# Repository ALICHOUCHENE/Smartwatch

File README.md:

<div align="center"><h1 style="font-family: courier;" align="center"></h1></div>

# Description
Smartwatch circuit for health and fitness
This robust fitness watch was designed for football players who leads an active lifestyle and values health and well-being. 
The watch creates for a personal training plan that adapts to some fitness needs. 
This smart-watch will provide a real-time guidance while exercising to help the player at the right intensity.
24/7 activity tracking with steps, calories and sleep, together with stress and recovery monitoring, provide a real time heart rate monitoring and help to maintain a healthy balance between activity and rest.

Here the features of the board:

- Xtensa dual-core 32-bit LX6 microprocessor(WROOM-32D) is the CPU of the board. operating at 240 MHz.
- Optical Sensor IC,BH1792GLC, a heart rate monitor module integrated with LED driver, green light, and IR detection photodiode.
- 1Cell / 3.7V 230mA Battery Management System / BMS Over Voltage, Over Current, Short Circuit Protection Module for Lithium ION Batterie.
- UART programming interface.
- I2C interface for OLED display.
- USB port for charging.

# PCB Layout : 

# Board 3D view : 

# Final Poduct : 

 # Manufacturing
 
After finishing the Routing and verify the pcb. We made the board at JLC PCB and we chose also the PCB Assembly service.
Here is the **[BOM](https://github.com/ALICHOUCHENE/Smartwatch-/blob/main/Assembly/BOM.csv)** needed for jlcpcb assembly service:

| Designator | Value           | Footprint                                                                        | LCSC Part |
|------------|-----------------|----------------------------------------------------------------------------------|-----------|
| U2         | TP4056          | Package_SO:SO-8_3.9x4.9mm_P1.27mm                                                | C16581    |
| R5         | 1.2K            | 402                                                                              |  C25862   |
| R7         | 1K              | 402                                                                              | C11702    |
| R8         | 1K              | 402                                                                              | C11702    |
| R4         | 1K              | 402                                                                              | C11702    |
| C2         | 0.1UF           | 402                                                                              |  C1525    |
| R6         | 100             | 402                                                                              |  C25076   |
| C3         | 0.1UF           | 402                                                                              |  C1525    |
| U1         | FS8205A         | Package_SO:TSSOP-8_4.4x3mm_P0.65mm                                               | C16052    |
| R2         | 3.3K            | 402                                                                              |  C25890   |
| R3         | 3.3K            | 402                                                                              |  C25890   |
| R1         | 3.3K            | 402                                                                              |  C25890   |
| C4         | 100nF           | 402                                                                              |  C1525    |
| R9         | 10K             | 402                                                                              |  C25744   |
| U4         | ESP32-WROOM-32D | RF_Module:ESP32-WROOM-32                                                         |           |
| U3         | DW01-P          | Package_TO_SOT_SMD:SOT-23-6                                                      | C181096   |
| C1         | 0.1UF           | 402                                                                              |  C1525    |
| J1         | USB_OTG         | Connector_USB:USB_Mini-B_Lumberg_2486_01_Horizontal                              | C136451   |
| BZ1        | Buzzer          | Buzzer_Beeper:Buzzer_Murata_PKMCS0909E4000-R1                                    | C255319   |
| R11        | 330             | 402                                                                              |  C25104   |
| R10        | 330             | 402                                                                              |  C25104   |
| SW1        | SW_DIP_x01      | Button_Switch_SMD:SW_DIP_SPSTx01_Slide_6.7x4.1mm_W6.73mm_P2.54mm_LowProfile_JPin | C54948    |
| D2         | LED             | 402                                                                              |           |
| D4         | LED             | 402                                                                              |           |
| D3         | LED             | 402                                                                              |           |
| Q2         | BC847           | Package_TO_SOT_SMD:SOT-23                                                        | C8664     |
| Q3         | BC847           | Package_TO_SOT_SMD:SOT-23                                                        | C8664     |
| U5         | AMS1117-3.3     | Package_TO_SOT_SMD:TSOT-23                                                       | C83932    |
| C5         | 0.1UF           | 402                                                                              |  C1525    |

# Downloads

* [Board schematics](https://github.com/ALICHOUCHENE/Smartwatch-/blob/main/Schematic.pdf)

* [PCB layout](https://github.com/ALICHOUCHENE/Smartwatch-/blob/main/Smartwatch.kicad_pcb)

* [BOM](https://github.com/ALICHOUCHENE/Smartwatch-/blob/main/Assembly/BOM.csv)

* [Position file](https://github.com/ALICHOUCHENE/Smartwatch-/blob/main/Assembly/Smartwatch-all-pos.csv)

* [Gerber File](https://github.com/ALICHOUCHENE/Smartwatch-/blob/main/Gerber/Gerber.rar)

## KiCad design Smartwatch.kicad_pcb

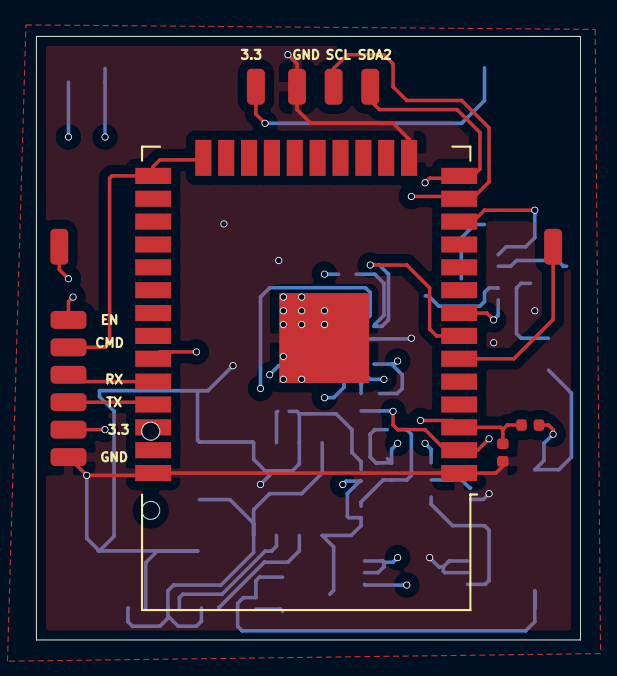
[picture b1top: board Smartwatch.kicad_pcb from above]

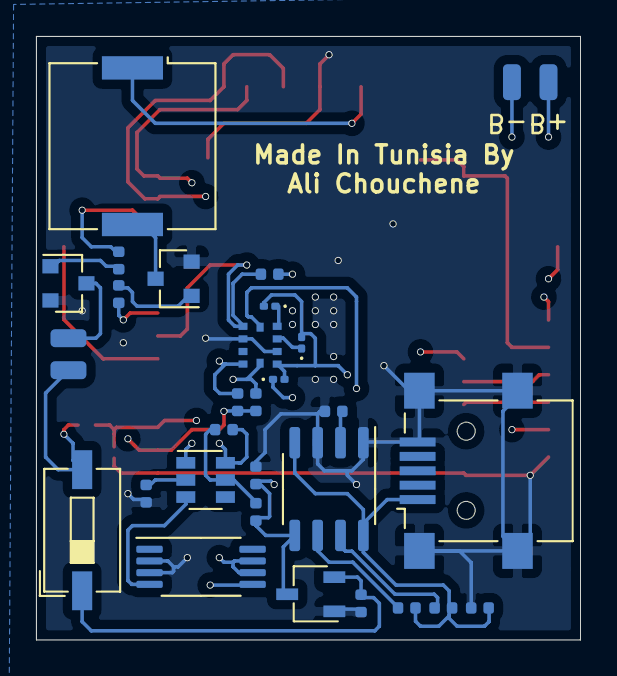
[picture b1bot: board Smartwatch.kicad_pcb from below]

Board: 4 copper layers, 30.2 x 33.5 mm, 46 parts (31 on the bottom side), 31 nets.

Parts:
BZ1: Buzzer; Buzzer_Murata_PKMCS0909E4000-R1
C1, C2, C3, C5: 0.1UF; C_0402_1005Metric
C4: 100nF; C_0402_1005Metric
D2, D3, D4: LED; LED_0201_0603Metric
IC1: BH1792GLC-E2; WLG
J1: USB_OTG; USB_Mini-B_Lumberg_2486_01_Horizontal
J2, J3, J4, J5, J6, J7, J8, J9, J10, J11, J12, J13, J14, J15, J16, J17: Conn_01x01_Female; SolderWirePad_1x01_SMD_1x2mm
Q2, Q3: BC847; SOT-23
R1, R2, R3: 3.3K; R_0402_1005Metric
R4, R7, R8: 1K; R_0402_1005Metric
R5: 1.2K; R_0402_1005Metric
R6: 100; R_0402_1005Metric
R9: 10K; R_0402_1005Metric
R10, R11: 330; R_0402_1005Metric
SW1: SW_DIP_x01; SW_DIP_SPSTx01_Slide_6.7x4.1mm_W6.73mm_P2.54mm_LowProfile_J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
U1: FS8205A; TSSOP-8_4.4x3mm_P0.65mm
U2: TP4056; SO-8_3.9x4.9mm_P1.27mm
U3: DW01-P; SOT-23-6
U4: ESP32-WROOM-32D; ESP32-WROOM-32
U5: AMS1117-3.3; TSOT-23

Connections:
+3V3: BZ1.1, D2.2, D3.2, D4.2, IC1.1, J4.1, J8.1, J16.1, R1.1, R2.1, R3.1, R9.1, SW1.2, U4.2
+5V: C1.1, J1.1, R7.1, R8.1, U2.4, U2.8
B1: J3.1, U4.6
B2: J2.1, U4.33
B+: C3.1, J14.1, R6.1, U2.5, U5.3
B-: C2.1, J13.1, U1.6, U1.7, U3.6
CMD: J11.1, U4.24, U4.25
EN: C4.1, J12.1, R9.2, U4.3
GND: C1.2, C3.2, C4.2, C5.2, IC1.2, IC1.7, J1.5, J1.6, J5.1, J15.1, Q2.2, Q3.2, R4.2, R5.1, U1.2, U1.3, U2.1, U2.3, U4.1, U4.15, U4.38, U4.39, U5.1
unnamed: BZ1.2, Q3.3
unnamed: C2.2, R6.2, U3.5
unnamed: C5.1, SW1.1, U5.2
unnamed: D2.1, IC1.3
unnamed: D3.1, IC1.4
unnamed: D4.1, IC1.5
unnamed: J17.1, Q2.3
unnamed: Q2.1, R10.1
unnamed: Q3.1, R11.1
unnamed: R4.1, U3.2
unnamed: R5.2, U2.2
unnamed: R7.2, U2.7
unnamed: R8.2, U2.6
OC: U1.4, U3.3
OD: U1.5, U3.1
RX: J10.1, U4.34
SC: IC1.6, R1.2, U4.7
SCL: IC1.10, J7.1, R3.2, U4.13
SDA2: IC1.9, J6.1, R2.2, U4.14
TX: J9.1, U4.35
bz: R11.2, U4.8
mt: R10.2, U4.12

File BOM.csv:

Designator,value,footprint,LCSC Part 
U2,TP4056,Package_SO:SO-8_3.9x4.9mm_P1.27mm,C16581
R5,1.2K,402, C25862
R7,1K,402,C11702
R8,1K,402,C11702
R4,1K,402,C11702
C2,0.1UF,402, C1525
R6,100,402, C25076
C3,0.1UF,402, C1525
U1,FS8205A,Package_SO:TSSOP-8_4.4x3mm_P0.65mm,C16052
R2,3.3K,402, C25890
R3,3.3K,402, C25890
R1,3.3K,402, C25890
C4,100nF,402, C1525
R9,10K,402, C25744
U4,ESP32-WROOM-32D,RF_Module:ESP32-WROOM-32,
U3,DW01-P,Package_TO_SOT_SMD:SOT-23-6,C181096
C1,0.1UF,402, C1525
J1,USB_OTG,Connector_USB:USB_Mini-B_Lumberg_2486_01_Horizontal,C136451
BZ1,Buzzer,Buzzer_Beeper:Buzzer_Murata_PKMCS0909E4000-R1,C255319
R11,330,402, C25104
R10,330,402, C25104
SW1,SW_DIP_x01,Button_Switch_SMD:SW_DIP_SPSTx01_Slide_6.7x4.1mm_W6.73mm_P2.54mm_LowProfile_JPin,C54948
D2,LED,402,
D4,LED,402,
D3,LED,402,
Q2,BC847,Package_TO_SOT_SMD:SOT-23,C8664
Q3,BC847,Package_TO_SOT_SMD:SOT-23,C8664
U5,AMS1117-3.3,Package_TO_SOT_SMD:TSOT-23,C83932
C5,0.1UF,402, C1525

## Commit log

2021-04-06 Create schematic
2021-04-06 Create Assembly
2021-04-06 Create final
2021-04-06 Create readme.
